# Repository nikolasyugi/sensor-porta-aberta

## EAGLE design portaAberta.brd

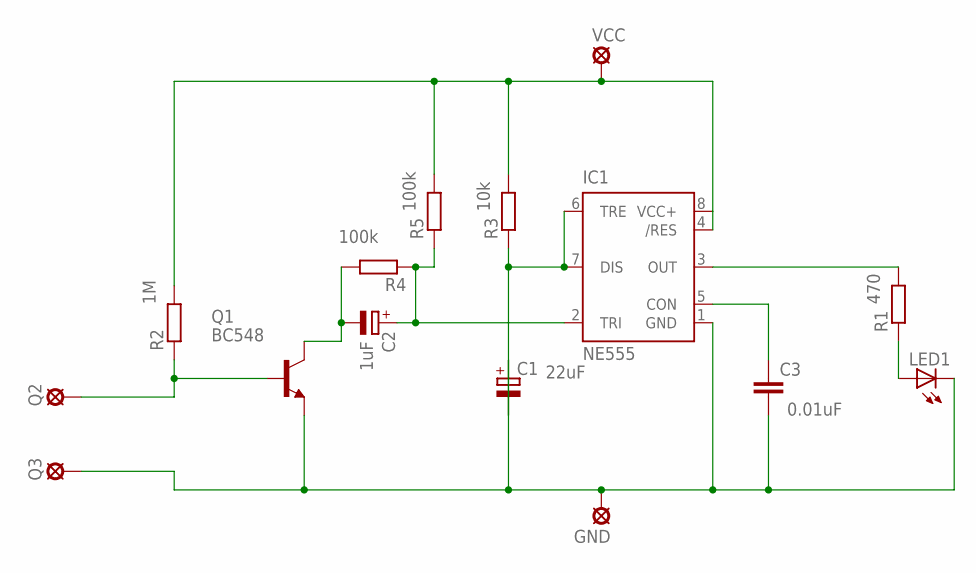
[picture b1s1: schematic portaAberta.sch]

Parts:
C1, C2: CPOL-EUE2.5-6; E2,5-6
C3: C-EU025-024X044; C025-024X044
GND: LSP10
IC1: NE555; DIL-08
LED1: LED5MM
Q1: BC548; TO92-EBC
Q2, Q3: LSP10
R1, R2, R3, R4, R5: R-EU_0207/10; 0207/10
VCC: LSP10

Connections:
9V: IC1.4 (/RES), IC1.8 (VCC+), R2.2, R3.2, R5.2, VCC.MP
GND: C1.+, C3.2, GND.MP, IC1.1 (GND), LED1.K (C), Q1.E, Q3.MP
unnamed: LED1.A, R1.1
unnamed: IC1.3 (OUT), R1.2
unnamed: C3.1, IC1.5 (CON)
unnamed: Q1.B, Q2.MP, R2.1
unnamed: C2.-, Q1.C, R4.2
unnamed: C2.+, IC1.2 (TRI), R4.1, R5.1
unnamed: C1.-, IC1.6 (TRE), IC1.7 (DIS), R3.1

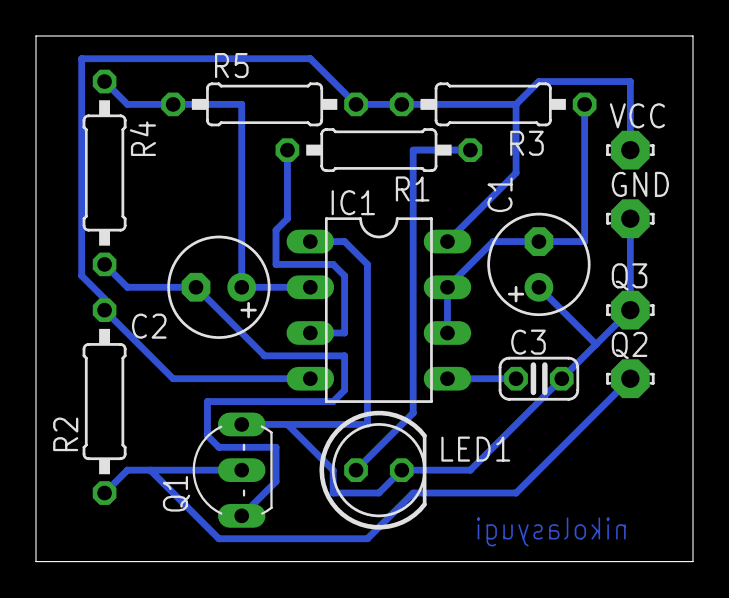
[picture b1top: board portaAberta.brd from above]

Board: 2 copper layers, 36.5 x 29.2 mm, 15 parts (0 on the bottom side), 9 nets.
